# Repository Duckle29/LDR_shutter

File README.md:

# LDR shutter release

This is a simple PCB entirely inspired by the resinlapse cable.
This should simplify the process, by removing the need to solder the sensor to a cable.

# JLCPCB ordering
The "production" folder has files ready to let you order these assembled from JLCPCB. If people need help walking through that process, open an issue and I'll help :)

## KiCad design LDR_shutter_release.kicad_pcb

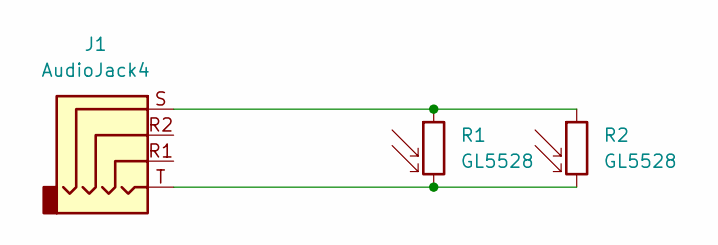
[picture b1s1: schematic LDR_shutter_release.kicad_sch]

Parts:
J1: AudioJack4; Jack_3.5mm_PJ320D_Horizontal; LCSC C431535
R1, R2: GL5528; R_LDR_5.1x4.3mm_P3.4mm_Vertical; LCSC C125627

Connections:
unnamed: J1.S, R1.1, R2.1
unnamed: J1.T, R1.2, R2.2

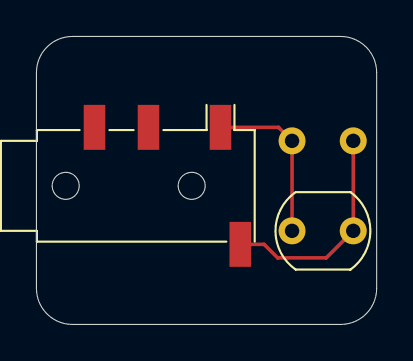
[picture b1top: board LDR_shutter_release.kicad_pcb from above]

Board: 2 copper layers, 18.9 x 16.0 mm, 3 parts (1 on the bottom side), 2 nets.

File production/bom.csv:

Designator,Footprint,Quantity,Value,LCSC Part #
J1,Jack_3.5mm_PJ320D_Horizontal,1,AudioJack4,C431535
"R1, R2",R_LDR_5.1x4.3mm_P3.4mm_Vertical,2,GL5528,C125627

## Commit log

2024-06-16 Added footprint for second LDR, to allow full JLC PCBA of top-side
2024-06-16 Regenerated gerbers
